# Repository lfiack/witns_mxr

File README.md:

# witns_mxr
4 voice mixer for my rack

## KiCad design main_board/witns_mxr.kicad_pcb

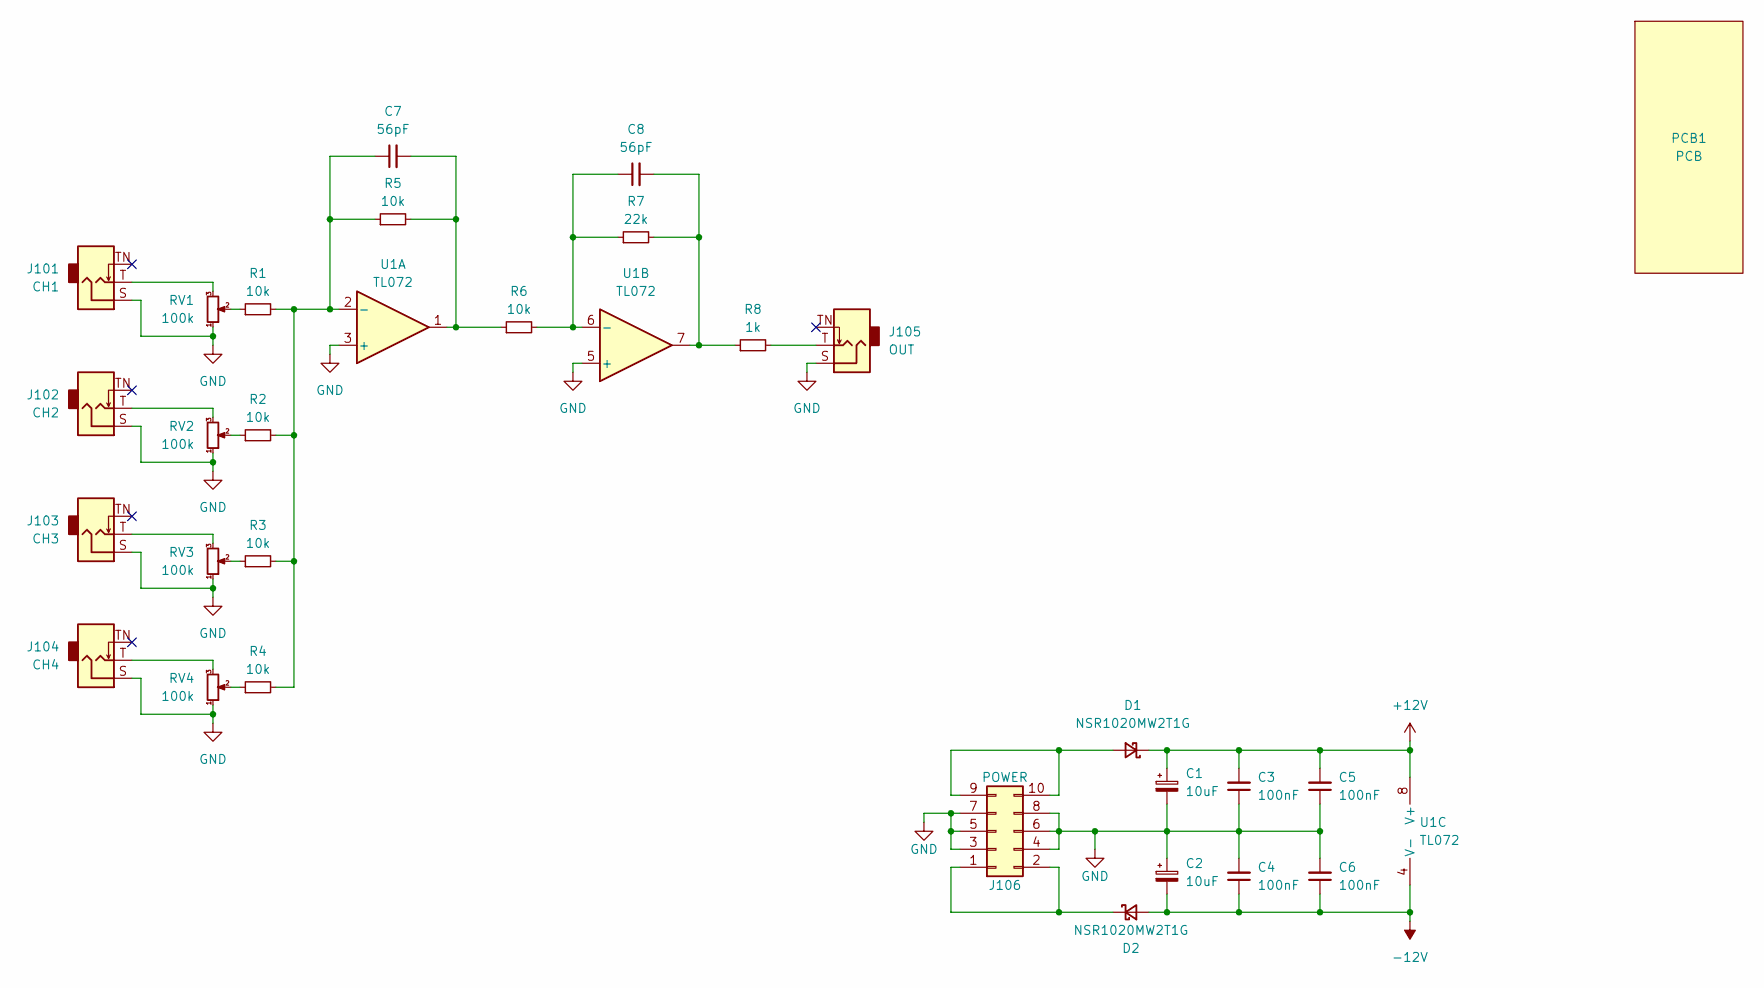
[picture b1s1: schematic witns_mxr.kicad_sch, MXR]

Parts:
C1, C2: 10uF; CP_Elec_4x5.4; Farnell 2611379
C3, C4, C5, C6: 100nF; C_0603_1608Metric
C7, C8: 56pF; C_0603_1608Metric
D1, D2: NSR1020MW2T1G; D_SOD-323; Farnell 1431027
J101: CH1
J102: CH2; Jack_3.5mm_QingPu_WQP-PJ398SM_Vertical_CircularHoles
J103: CH3; Jack_3.5mm_QingPu_WQP-PJ398SM_Vertical_CircularHoles
J104: CH4; Jack_3.5mm_QingPu_WQP-PJ398SM_Vertical_CircularHoles
J105: OUT; Jack_3.5mm_QingPu_WQP-PJ398SM_Vertical_CircularHoles
J106: POWER; PinHeader_2x05_P2.54mm_Vertical_SMD
PCB1: PCB; PCB_4HP
R1, R2, R3, R4, R5, R6: 10k; R_0603_1608Metric
R7: 22k; R_0603_1608Metric
R8: 1k; R_0603_1608Metric
RV1, RV2, RV3, RV4: 100k; Potentiometer_Alpha_RD901F-40-00D_Single_Vertical
U1: TL072; SOIC-8_3.9x4.9mm_P1.27mm

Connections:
+12V: C1.1, C3.2, C5.2, D1.1 (K), U1.8 (V+)
-12V: C2.2, C4.1, C6.1, D2.2 (A), U1.4 (V-)
GND: C1.2, C2.1, C3.1, C4.2, C5.1, C6.2, J101.S, J102.S, J103.S, J104.S, J105.S, J106.3, J106.4, J106.5, J106.6, J106.7, J106.8, RV1.1, RV2.1, RV3.1, RV4.1, U1.3 (+), U1.5 (+)
unnamed: J101.T, RV1.3
unnamed: J102.T, RV2.3
unnamed: J103.T, RV3.3
unnamed: J104.T, RV4.3
unnamed: J105.T, R8.2
unnamed: D2.1 (K), J106.1, J106.2
unnamed: D1.2 (A), J106.9, J106.10
unnamed: R1.1, RV1.2
unnamed: R2.1, RV2.2
unnamed: R3.1, RV3.2
unnamed: R4.1, RV4.2
unnamed: C7.2, R5.2, R6.1, U1.1
unnamed: C7.1, R1.2, R2.2, R3.2, R4.2, R5.1, U1.2 (-)
unnamed: C8.1, R6.2, R7.1, U1.6 (-)
unnamed: C8.2, R7.2, R8.1, U1.7

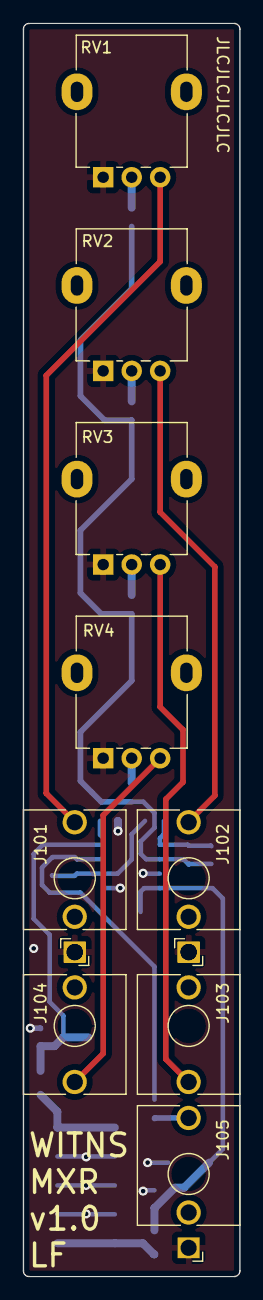
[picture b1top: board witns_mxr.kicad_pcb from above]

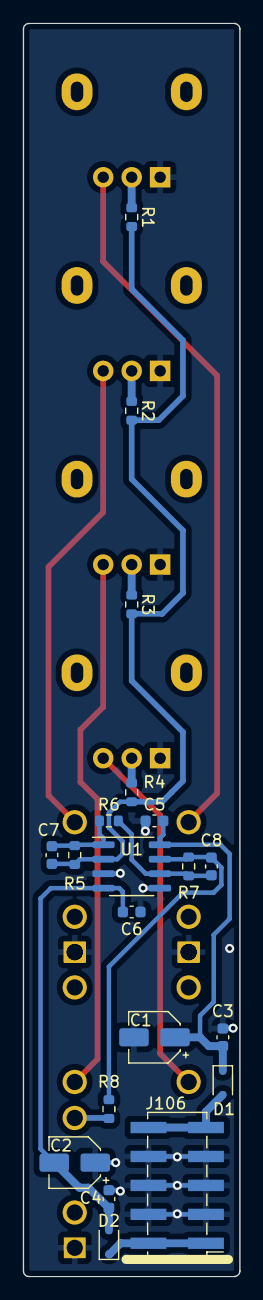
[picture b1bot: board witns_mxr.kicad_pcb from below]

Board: 2 copper layers, 19.0 x 110.0 mm, 30 parts (20 on the bottom side), 18 nets.

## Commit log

2023-01-19 First attempt at face plate
2023-01-22 main board
2023-01-23 faceplate
2023-01-25 added white line for -12V
2023-01-25 correction on faceplace
2023-01-29 JLC mark
2023-01-29 fabrication files
